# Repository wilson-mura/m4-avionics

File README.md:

# Martlet IV Avionics

This repository contains all the avionics for Martlet 4, including system 
design, documentation, schematics, PCBs, and firmware.

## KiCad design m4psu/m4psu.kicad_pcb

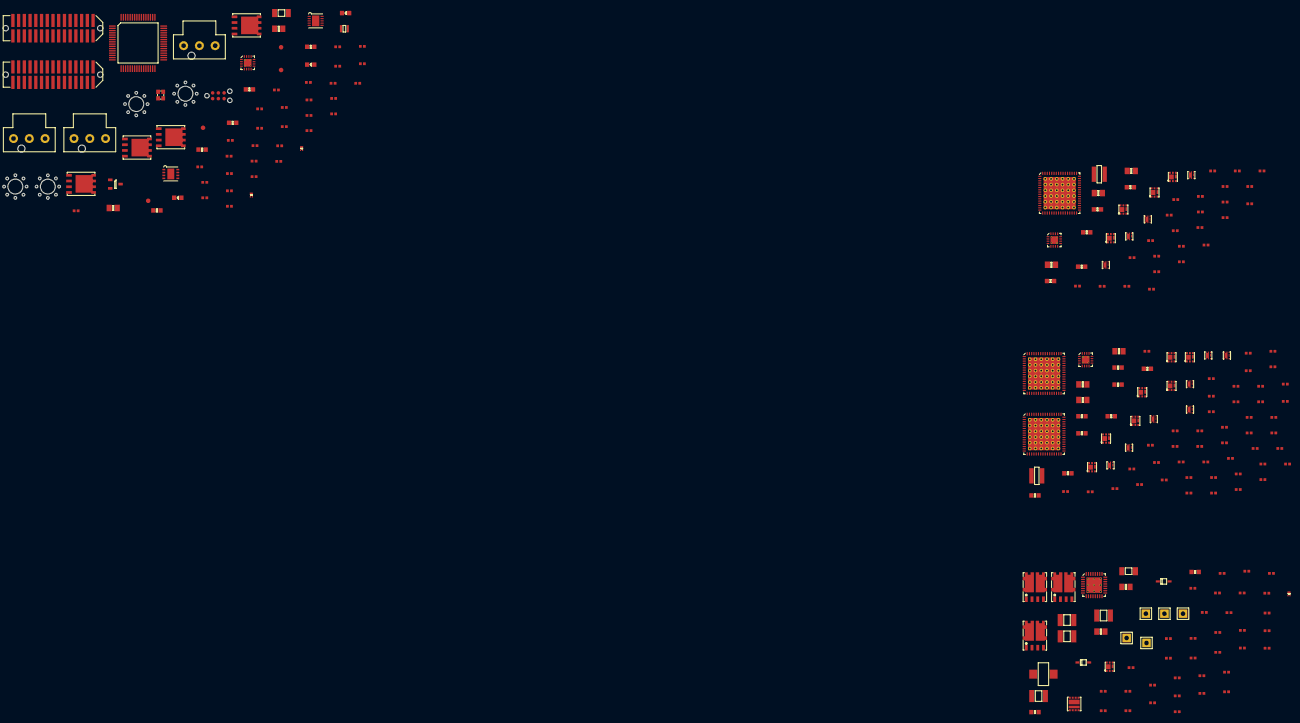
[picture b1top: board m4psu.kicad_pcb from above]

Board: 2 copper layers, 246 parts (0 on the bottom side), 161 nets, no tracks yet.

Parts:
C1, C2: 10p; 0402
C3, C5, C6, C8, C9, C10, C11, C22, C25, C29, C30, C32, C33, C34, C37, C42, C45, C46, C49, C50, C51, C52, C54, C55, C56, C57, C58: 100n; 0402
C4: 4µ7; 0402
C7, C43, C48: 1µ; 0402
C12, C13: 2µ2; 0402
C14, C17: 22µ; 0805
C15, C18, C19, C20, C23, C38: 100n; 0603
C16, C26, C39: 3n3; 0402
C21, C35: 10u; 0805
C24, C31, C36: 10n; 0402
C27, C28, C40, C41: 22u; 0805
C44, C64: 2µ2; 0805
C47: 1µ5; 0603
C53: 100p; 0402
C59, C60, C62, C63: 10µ; 1210
C61: 22p; 0402
D1: RED; 0603-LED
D2: YLW; 0603-LED
D3: GRN; 0603-LED
D4, D5: SCHOTTKY; SOD-323
IC1: MCP2562; DFN-8-EP-MICROCHIP
IC2: STM32F405RxTx; LQFP-64
IC3: TPS62152; QFN-16-EP-TI
IC4: LTC4151; DFN-10-EP-LT
IC5: TLV76012; SOT-23
IC6: TPS62132; QFN-16-EP-TI
IC7, IC8, IC10: LTC2975; QFN-64-EP-LTC-UP
IC9: TPS62133; QFN-16-EP-TI
IC11: BQ40Z60; QFN-32-EP-TI
J1: WEST TOP; TFML-115-02-L-D-LC
J2: EAST TOP; TFML-115-02-L-D-LC
J3: SUPPLY; ULTRA-FIT-01x03
J4: VALVES; ULTRA-FIT-01x03
J5: CHG; ULTRA-FIT-01x03
J6: BAT+; SIL-254P-01
J7: TAP3; SIL-254P-01
J8: TAP2; SIL-254P-01
J9: TAP1; SIL-254P-01
J10: BAT-; SIL-254P-01
L1: 3µ3; VLS201610HBX-1
L2, L3: 2u2; XFL4020
L4: 2µ2; SRP5030T
P1: SWD_TC; TC2030-NL
Q1, Q2, Q3, Q5: PFET; PowerPAK-SO-8
Q4, Q6, Q33: NFET; SOT-883-B
Q7, Q9, Q11, Q13, Q15, Q17, Q19, Q21, Q23, Q25, Q27: NFET; PowerPAK-SC-75-6L-Single
Q8, Q10, Q12, Q14, Q16, Q18, Q20, Q22, Q24, Q26, Q28: PFET; SON2x2
Q29, Q30, Q32: NFET2; PowerFLAT-5x6
Q31: SiZ340DT; PowerPair-3x3
Q34: NFET; SON2x2N
R1, R2: 100k; 0402
R3, R5, R6, R7: 100; 0402
R4, R8, R9: 4k7; 0402
R10, R98: 2m; 1206
R11, R15: 47k; 0402
R12, R16, R19, R20, R21, R22, R23, R25, R26, R31, R32, R33, R34, R35, R37, R38, R63, R64, R65, R66, R67, R69, R70: 10k; 0402
R13, R14, R17, R18, R27, R29, R39, R41, R43, R45, R47, R49, R51, R53, R55, R57, R59, R61, R71, R73, R75, R77, R79, R81, R83, R85: 33k; 0402
R24, R36, R68: 5k49; 0402
R28, R40, R44, R48, R52, R56, R60, R72, R76, R80, R84: 1M; 0402
R30, R42, R46, R50, R54, R58, R62, R74, R78, R82, R86, R99: 10m; 0603
R87, R88, R92, R93, R94, R95: 100R; 0402
R89, R100, R105: 10M; 0402
R90, R96, R104: 5K1; 0402
R91, R97: 10R; 0402
R101: 330K; 0402
R102: 56K2; 0402
R103: 10K; 0402
R106: 100K; 0402
R107: 2R; 0402
R108: 120; 0603
TP1, TP2, TP3, TP4: TESTPAD
X1, X2, X3, X4: HOLE; M3_MOUNT
Y1: 26M; XTAL-20x16

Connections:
3v3: C4.2, C5.2, C6.2, C7.2, C8.2, C9.2, C10.2, C11.2, C17.2, IC1.5, IC2.1, IC2.13, IC2.19, IC2.32, IC2.48, IC2.64, IC3.7, IC3.14, L1.2, P1.1, R1.2, R4.2, R8.2, R9.2
3v3_B: C22.2, C27.1, C28.1, C30.2, C34.2, IC6.14, IC7.9, IC7.10, IC7.11, IC7.12, IC7.55, IC7.56, IC8.9, IC8.10, IC8.11, IC8.12, IC8.35, IC8.55, IC8.56, IC10.10, IC10.11, IC10.12, L2.2, Q8.S, Q10.S, Q12.S, Q14.S, Q16.S, Q18.S, Q20.S, R19.1, R20.1, R21.1, R22.1, R23.1, R24.1, R25.1, R26.1, R27.1, R29.1, R31.1, R32.1, R33.1, R34.1, R35.1, R36.1, R37.1, R38.1, R39.1, R41.1, R43.1, R45.1, R47.1, R49.1, R51.1, R53.1, R55.1, R57.1, R59.1, R61.1, R63.1, R64.1, R65.1, R66.1, R67.1, R68.1, R69.1, R70.1
5v_B: C40.1, C41.1, IC9.14, IC10.9, IC10.55, IC10.56, L3.2, Q22.S, Q24.S, Q26.S, Q28.S, R71.1, R73.1, R75.1, R77.1, R79.1, R81.1, R83.1, R85.1
/3v3/ISNS0+: IC7.1, IC7.41, Q8.D, R30.2
/3v3/ISNS1+: IC7.43, IC7.63, Q10.D, R42.2
/3v3/ISNS2+: IC7.45, IC7.61, Q12.D, R46.2
/3v3/ISNS3+: IC7.47, IC7.49, Q14.D, R50.2
/3v3/ISNS4+: IC8.1, IC8.41, Q16.D, R54.2
/3v3/ISNS5+: IC8.43, IC8.63, Q18.D, R58.2
/3v3/ISNS6+: IC8.45, IC8.61, Q20.D, R62.2
/3v3/VEN_0: IC7.3, Q7.G, R27.2, R28.1
/3v3/VEN_1: IC7.4, Q9.G, R39.2, R40.1
/3v3/VEN_2: IC7.5, Q11.G, R43.2, R44.1
/3v3/VEN_3: IC7.6, Q13.G, R47.2, R48.1
/3v3/VEN_4: IC8.3, Q15.G, R51.2, R52.1
/3v3/VEN_5: IC8.4, Q17.G, R55.2, R56.1
/3v3/VEN_6: IC8.5, Q19.G, R59.2, R60.1
/3v3_AUX1: IC8.44, J1.15, R58.1
/3v3_AUX2: IC8.46, J1.17, R62.1
/3v3_DL: IC7.44, J1.7, R42.1
/3v3_FC: IC7.46, J1.9, R46.1
/3v3_PYRO: IC8.42, J1.13, R54.1
/3v3_RADIO: IC7.48, J1.11, R50.1
/3v3_TOP: IC7.42, J1.5, R30.1
/5v/ISNS7+: IC10.1, IC10.41, Q22.D, R74.2
/5v/ISNS8+: IC10.43, IC10.63, Q24.D, R78.2
/5v/ISNS9+: IC10.45, IC10.61, Q26.D, R82.2
/5v/ISNS10+: IC10.47, IC10.49, Q28.D, R86.2
/5v/VEN_7: IC10.3, Q21.G, R71.2, R72.1
/5v/VEN_8: IC10.4, Q23.G, R75.2, R76.1
/5v/VEN_9: IC10.5, Q25.G, R79.2, R80.1
/5v/VEN_10: IC10.6, Q27.G, R83.2, R84.1
/5v_AUX1: IC10.44, J2.17, R78.1
/5v_AUX2: IC10.46, J2.19, R82.1
/5v_CAM1: IC10.48, J2.21, J2.23, R86.1
/5v_CAN: C3.1, IC1.3, J1.22
/5v_RADIO: IC10.42, J2.15, R74.1
/12v_DIV: IC2.21, R11.2, R12.1
/12v_DL: C20.2, IC5.1, J2.13, R11.1
/CAN+: IC1.7, J1.26, R108.2
/CAN-: IC1.6, J1.24, R108.1
/CAN_RXD: IC1.4, IC2.61
/CAN_TXD: IC1.1, IC2.62
/EN_POWER: IC2.43, Q6.G, R18.1
/EN_PYRO: IC2.16, Q4.G, R14.2
/JTCK: IC2.49, J1.8, P1.4
/JTDI: IC2.50, J1.10
/JTDR: IC2.55, J1.12
/JTMS: IC2.46, J1.6, P1.2
/LED_GRN: IC2.11, R7.1
/LED_RED: IC2.9, R5.1
/LED_YLW: IC2.10, R6.1
/PWR: J2.25, R1.1, R2.1
/PYRO_SO: J3.1, J3.2, J3.3, Q1.D, Q2.D, Q3.D, R15.1
/SCL: IC2.41, IC4.6, IC7.30, IC8.30, IC10.30, R8.1, R88.1, TP2.1
/SDA: IC2.40, IC4.7, IC7.29, IC8.29, IC10.29, R4.1, R87.1, TP1.1
/SO_DIV: IC2.22, R15.2, R16.1
/V_SHORE: J5.1, J5.2, Q33.S, Q34.S, R103.2, R105.1, R106.1, R107.1
/charger/ACFET: IC11.29, R104.2
/charger/ACP: IC11.31, R103.1
/charger/BATT1: J9.1, R95.2
/charger/BATT2: J8.1, R94.2
/charger/BATT3: J7.1, R93.2
/charger/BATT4: C45.1, J6.1, Q29.S1, Q29.S2, Q30.S1, R89.1, R92.2, R97.2
/charger/CHG: IC11.32, R90.2
/charger/DSG: IC11.30, R96.2
/charger/VCHARGE: C62.2, C63.2, Q31.D1, Q34.D, R91.2
/~ALERT: IC2.42, IC7.31, IC8.31, IC10.31, IC11.14, R9.1, TP3.1
/~RST: IC2.7, P1.3
/~WAKE: IC2.14, R2.2
GND: C1.1, C2.1, C3.2, C4.1, C5.1, C6.1, C7.1, C8.1, C9.1, C10.1, C11.1, C12.2, C13.2, C14.1, C15.1, C16.1, C17.1, C18.1, C19.1, C20.1, C21.2, C22.1, C23.2, C24.1, C25.1, C26.2, C27.2, C28.2, C30.1, C31.1, C32.1, C34.1, C35.2, C36.1, C37.1, C38.2, C39.2, C40.2, C41.2, C53.2, C54.2, C59.2, C60.2, C62.1, C63.1, C64.2, D1.1, D2.1, D3.1, IC1.2, IC1.8, IC1.EP, IC2.12, IC2.18, IC2.60, IC2.63, IC3.5, IC3.6, IC3.8, IC3.15, IC3.16, IC3.EP, IC4.3, IC4.4, IC4.5, IC4.9, IC4.EP, IC5.3, IC6.5, IC6.6, IC6.7, IC6.8, IC6.15, IC6.16, IC6.EP, IC7.2, IC7.15, IC7.16, IC7.19, IC7.20, IC7.21, IC7.27, IC7.28, IC7.34, IC7.36, IC7.37, IC7.39, IC7.50, IC7.52, IC7.59, IC7.60, IC7.62, IC7.64, IC7.EP, IC8.2, IC8.15, IC8.16, IC8.19, IC8.20, IC8.21, IC8.27, IC8.28, IC8.34, IC8.36, IC8.37, IC8.39, IC8.47, IC8.48, IC8.49, IC8.50, IC8.52, IC8.59, IC8.60, IC8.62, IC8.64, IC8.EP, IC9.5, IC9.6, IC9.7, IC9.8, IC9.15, IC9.16, IC9.EP, IC10.2, IC10.15, IC10.16, IC10.19, IC10.20, IC10.21, IC10.27, IC10.28, IC10.34, IC10.35, IC10.36, IC10.37, IC10.39, IC10.50, IC10.52, IC10.59, IC10.60, IC10.62, IC10.64, IC10.EP, IC11.7, IC11.24, J1.1, J1.2, J1.3, J1.4, J1.27, J1.28, J1.29, J1.30, J2.1, J2.2, J2.3, J2.4, J2.27, J2.28, J2.29, J2.30, J4.1, J4.2, J4.3, J5.3, P1.5, Q4.S, Q6.S, Q7.S, Q9.S, Q11.S, Q13.S, Q15.S, Q17.S, Q19.S, Q21.S, Q23.S, Q25.S, Q27.S, Q31.S2, Q33.G, R12.2, R14.1, R16.2, R18.2, R28.2, R40.2, R44.2, R48.2, R52.2, R56.2, R60.2, R72.2, R76.2, R80.2, R84.2, R98.1, R106.2, TP4.1, Y1.2, Y1.4
unnamed: C1.2, IC2.5, Y1.1
unnamed: C2.2, R3.1, Y1.3
unnamed: C12.1, IC2.47
unnamed: C13.1, IC2.31
unnamed: C16.2, IC3.9
unnamed: C24.2, IC7.51
unnamed: C25.2, IC7.13, IC7.14
unnamed: C26.1, IC6.9
unnamed: C29.1, IC7.38
unnamed: C29.2, IC7.40
unnamed: C31.2, IC8.51
unnamed: C32.2, IC8.13, IC8.14
unnamed: C33.1, IC8.38
unnamed: C33.2, IC8.40
unnamed: C36.2, IC10.51
unnamed: C37.2, IC10.13, IC10.14
unnamed: C39.1, IC9.9
unnamed: C42.1, IC10.38
unnamed: C42.2, IC10.40
unnamed: C43.2, IC11.22, R91.1
unnamed: C44.2, IC11.2
unnamed: C45.2, C55.2
unnamed: C46.1, D4.1, IC11.28
unnamed: C46.2, IC11.26, L4.2, Q31.S1D2
unnamed: C47.1, D4.2, IC11.23
unnamed: C48.1, D5.1, IC11.1
unnamed: C49.1, IC11.3, R92.1
unnamed: C49.2, C50.1, IC11.4, R93.1
unnamed: C50.2, C51.1, IC11.5, R94.1
unnamed: C51.2, C52.1, IC11.6, R95.1
unnamed: C56.2, C57.1, IC11.20, L4.1, R99.1
unnamed: C61.2, IC11.18, R101.2, R102.1
unnamed: C64.1, R107.2
unnamed: D1.2, R5.2
unnamed: D2.2, R6.2
unnamed: D3.2, R7.2
unnamed: D5.2, R97.1
unnamed: IC2.6, R3.2
unnamed: IC3.1, IC3.2, IC3.3, L1.1
unnamed: IC4.10, Q1.S, Q2.S, Q3.S, R10.1, R13.2
unnamed: IC6.1, IC6.2, IC6.3, L2.1
unnamed: IC7.18, R24.2
unnamed: IC7.22, R23.2
unnamed: IC7.23, R21.2
unnamed: IC7.24, R25.2
unnamed: IC7.25, R19.2
unnamed: IC7.26, R26.2
unnamed: IC7.32, R22.2
unnamed: IC7.33, R20.2
unnamed: IC8.18, R36.2
unnamed: IC8.22, R35.2
unnamed: IC8.23, R33.2
unnamed: IC8.24, R37.2
unnamed: IC8.25, R31.2
unnamed: IC8.26, R38.2
unnamed: IC8.32, R34.2
unnamed: IC8.33, R32.2
unnamed: IC9.1, IC9.2, IC9.3, L3.1
unnamed: IC10.18, R68.2
unnamed: IC10.22, R67.2
unnamed: IC10.23, R65.2
unnamed: IC10.24, R69.2
unnamed: IC10.25, R63.2
unnamed: IC10.26, R70.2
unnamed: IC10.32, R66.2
unnamed: IC10.33, R64.2
unnamed: IC11.16, R87.2
unnamed: IC11.17, R88.2
unnamed: IC11.25, Q31.G2
unnamed: IC11.27, Q31.G1
unnamed: Q1.G, Q2.G, Q3.G, Q4.D, R13.1
unnamed: Q5.G, Q6.D, R17.1
unnamed: Q7.D, Q8.G, R29.2
unnamed: Q9.D, Q10.G, R41.2
unnamed: Q11.D, Q12.G, R45.2
unnamed: Q13.D, Q14.G, R49.2
unnamed: Q15.D, Q16.G, R53.2
unnamed: Q17.D, Q18.G, R57.2
unnamed: Q19.D, Q20.G, R61.2
unnamed: Q21.D, Q22.G, R73.2
unnamed: Q23.D, Q24.G, R77.2
unnamed: Q25.D, Q26.G, R81.2
unnamed: Q27.D, Q28.G, R85.2
unnamed: Q29.D1, Q29.D2, Q30.D1, Q30.D2, Q32.D1, Q32.D2
unnamed: Q29.G1, Q29.G2, Q30.G1, R89.2, R90.1
unnamed: Q30.G2, Q32.G1, Q32.G2, R96.1, R100.2
unnamed: Q33.D, Q34.G, R104.1, R105.2
PGND: C43.1, C44.1, C47.2, C48.2, C52.2, C53.1, C54.1, C56.1, C58.1, IC11.8, IC11.9, IC11.21, IC11.EP, J10.1, R98.2, R102.2
VBATT: C14.2, C15.2, C18.2, C55.1, C57.2, C58.2, C59.1, C60.1, C61.1, IC3.10, IC3.11, IC3.12, IC3.13, IC4.1, IC4.2, IC11.19, Q5.S, Q30.S2, Q32.S1, Q32.S2, R10.2, R17.2, R99.2, R100.1, R101.1
VCC: C19.2, C21.1, C23.1, C35.1, C38.1, IC5.2, IC6.10, IC6.11, IC6.12, IC6.13, IC9.10, IC9.11, IC9.12, IC9.13, Q5.D

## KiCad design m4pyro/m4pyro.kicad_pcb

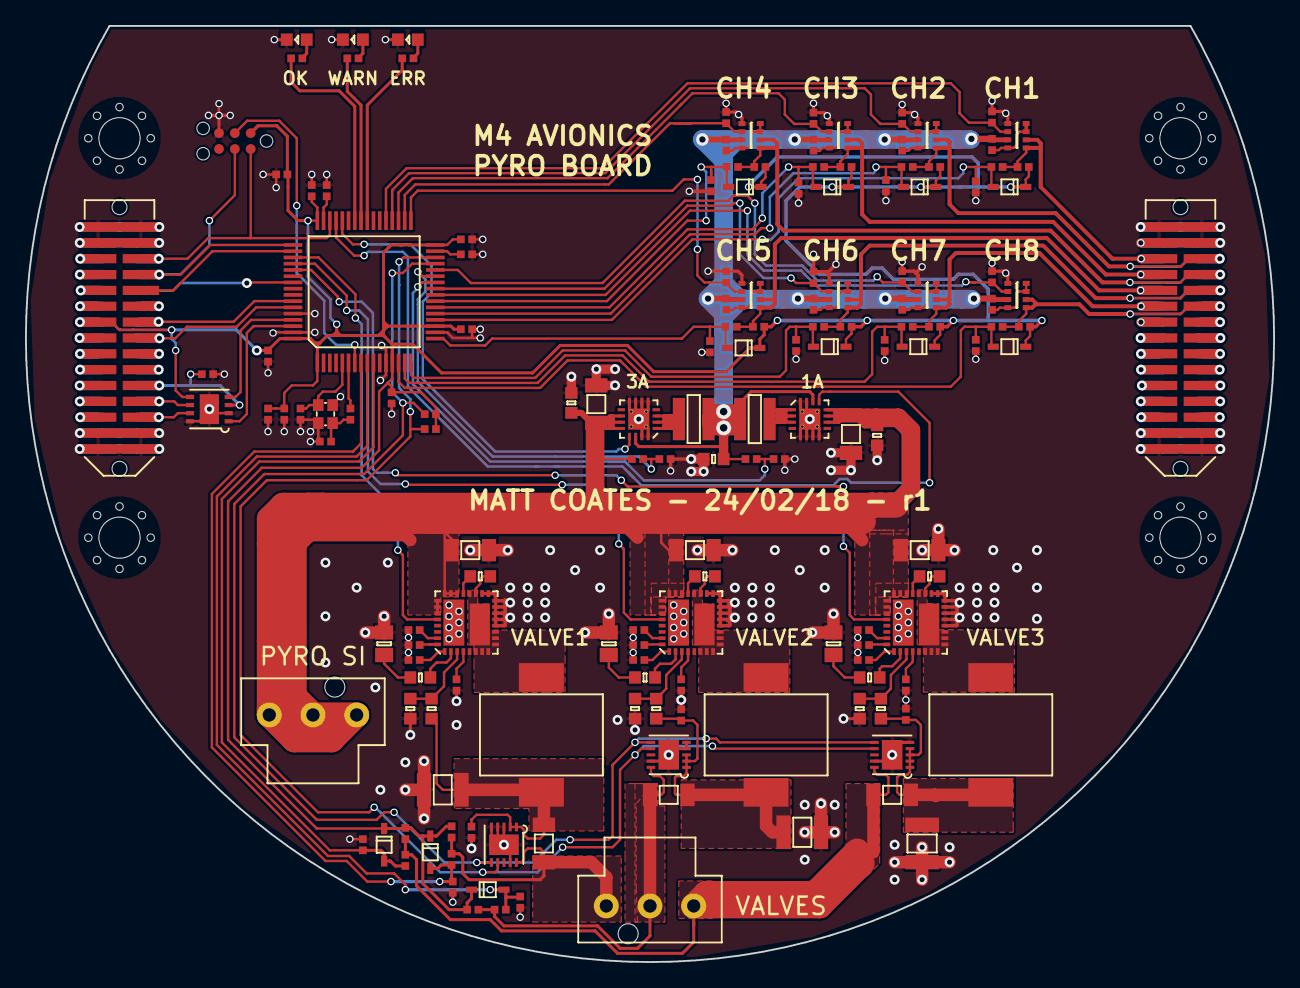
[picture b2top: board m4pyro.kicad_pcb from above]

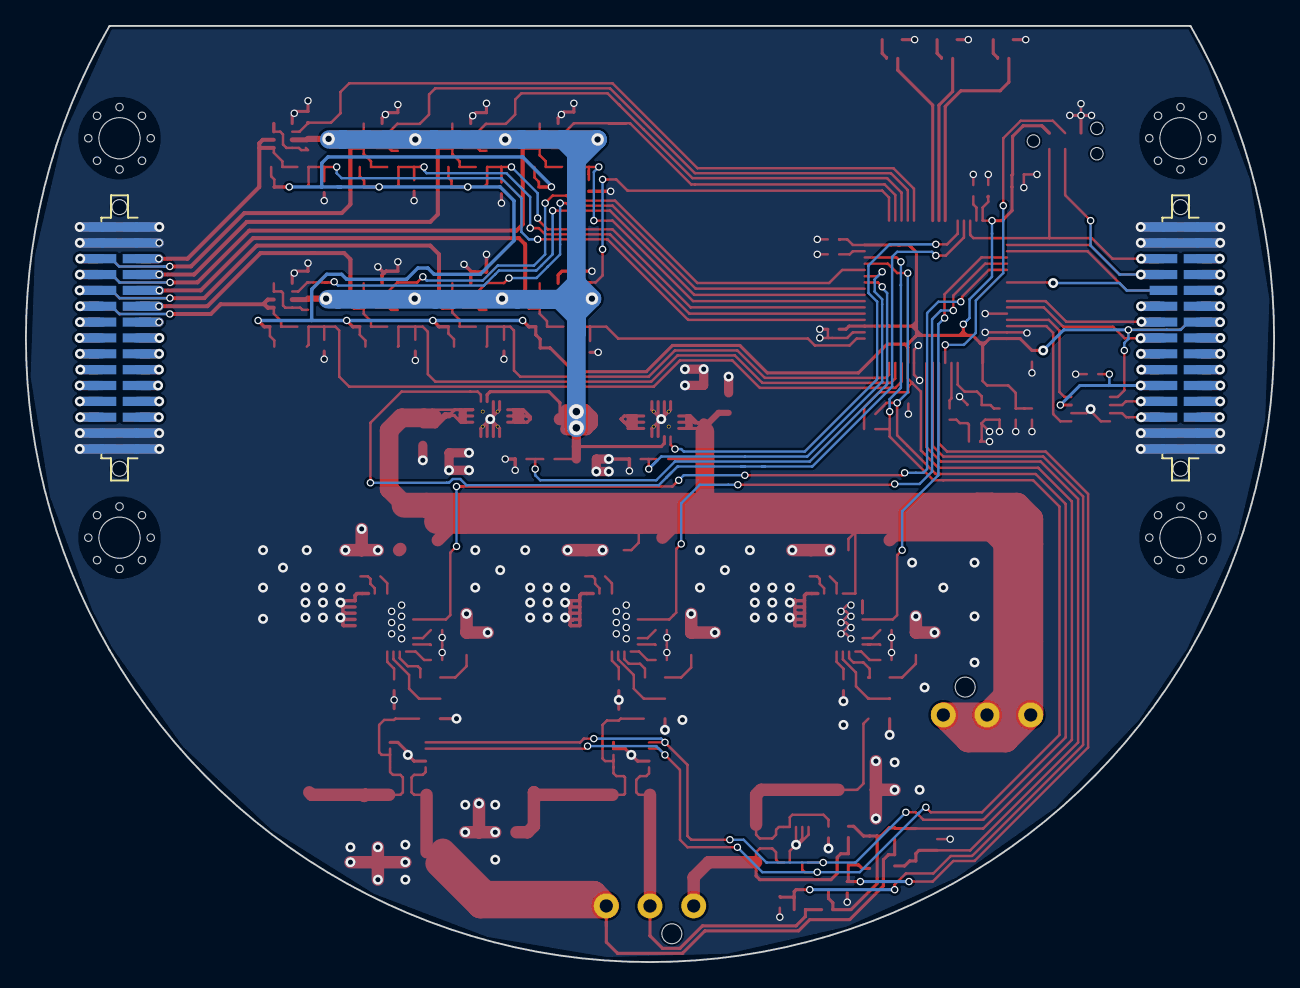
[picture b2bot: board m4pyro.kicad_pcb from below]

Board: 2 copper layers, 100.0 x 75.0 mm, 165 parts (2 on the bottom side), 133 nets.

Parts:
C1, C2: 10p; 0402
C3: 4µ7; 0402
C4, C5, C7, C8, C9, C10, C15, C19, C20, C21, C22, C23, C24, C25, C26, C29, C36, C43, C48, C49, C50: 100n; 0402
C6, C28, C35, C42: 1µ; 0402
C11, C18: 2µ2; 0402
C12, C14, C27, C34, C41: 10µ; 1206
C13, C17, C30, C37, C44: 100n; 0603
C16: 22µ; 0603
C31, C38, C45: 22n; 0402
C32, C39, C46: 1.2u; 0805
C33, C40, C47: 100µ; 1210
D1: RED; 0603-LED
D2: YLW; 0603-LED
D3: GRN; 0603-LED
D4, D5, D6, D7, D8, D9, D10, D11, D12, D13, D14: PMEG3005AEA; SOD-323
IC1: STM32F405RxTx; LQFP-64
IC2: TPS62133; QFN-16-EP-TI
IC3: MCP2562; DFN-8-EP-MICROCHIP
IC4: TPS62153; QFN-16-EP-TI
IC5, IC7, IC9: ADP2389; ADP2389ACPZ-R7
IC6, IC8, IC10: LTC4151; DFN-10-EP-LT
J1: WEST TOP; TFML-115-02-L-D-LC
J2: WEST BOT; SFML-115-02-L-D
J3: EAST TOP; TFML-115-02-L-D-LC
J4: EAST BOT; SFML-115-02-L-D
J5: SUPPLY; ultra-fit-01x03
J6: VALVES; ultra-fit-01x03
L1, L2: 2µ2; XFL4020
L3, L4, L5: 2µ2; WE-HCC-1090
P1: SWD_TC; TC2030-NL
Q1, Q2, Q3, Q4, Q5, Q6, Q7, Q8: Si5515CDC; ChipFET-1206-8
R1, R2, R3, R4: 100; 0402
R5, R9, R11, R12, R13, R14, R15, R16, R17, R18, R19, R20, R21, R22, R23, R24, R25, R26, R27, R28, R31, R32, R35, R36, R39, R40, R61, R62, R63: 10k; 0402
R6, R8, R29, R30, R33, R34, R37, R38, R58, R59, R60: 1k; 0402
R7: 47k; 0402
R10: 3k3; 0402
R41, R42: 4k7; 0402
R43, R48, R53: 100k; 0402
R44, R49, R54: 68k; 0603
R45, R50, R55: 47.5k; 0603
R46, R51, R56: 2.5k; 0603
R47, R52, R57: 5m; 1206
R64, R65, R66: 82.5k; 0402
X2, X3, X4, X5: HOLE; M3_MOUNT
Y1: 26M; XTAL-20x16

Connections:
3v3: C3.2, C4.2, C5.2, C6.2, C7.2, C8.2, C9.2, C10.2, D4.1, D5.1, D6.1, D7.1, D8.1, D9.1, D10.1, D11.1, D12.1, D13.1, D14.1, IC1.1, IC1.13, IC1.19, IC1.32, IC1.48, IC1.64, IC3.5, J1.13, J2.13, P1.1, R6.2, R8.2, R29.2, R30.2, R33.2, R34.2, R37.2, R38.2, R41.2, R42.2, R58.2, R59.2, R60.2
/1A_EN: IC1.45, IC4.13
/3A_EN: IC1.44, IC2.13
/3v3_AUX1: J1.15, J2.15
/3v3_AUX2: J1.17, J2.17
/3v3_DL: J1.7, J2.7
/3v3_FC: J1.9, J2.9
/3v3_RADIO: J1.11, J2.11
/3v3_TOP: J1.5, J2.5
/5v_AUX1: J3.17, J4.17
/5v_AUX2: J3.19, J4.19
/5v_CAM1: J3.21, J4.21
/5v_CAM2: J3.23, J4.23
/5v_CAN: C15.1, IC3.3, J1.22, J2.22
/5v_RADIO: J3.15, J4.15
/12v_DL: J3.13, J4.13
/BUS: C16.1, IC2.14, IC4.14, L1.2, L2.2, Q1.3, Q2.3, Q3.3, Q4.3, Q5.3, Q6.3, Q7.3, Q8.3, R9.1, R15.1, R16.1, R17.1, R18.1, R25.1, R26.1, R27.1, R28.1
/BUS_DIV: IC1.26, R9.2, R10.1
/CAN+: IC3.7, J1.26, J2.26
/CAN-: IC3.6, J1.24, J2.24
/CAN_RXD: IC1.61, IC3.4
/CAN_TXD: IC1.62, IC3.1
/CH1: IC1.37, Q7.2, R14.1
/CH1_CONT: C19.2, D4.2, IC1.20, R19.2
/CH2: IC1.36, Q6.2, R23.1
/CH2_CONT: C21.2, D6.2, IC1.21, R31.2
/CH3: IC1.35, Q5.2, R13.1
/CH3_CONT: C23.2, D8.2, IC1.22, R35.2
/CH4: IC1.34, Q8.2, R24.1
/CH4_CONT: C25.2, D10.2, IC1.23, R39.2
/CH5: IC1.33, Q3.2, R12.1
/CH5_CONT: C20.2, D5.2, IC1.17, R20.2
/CH6: IC1.25, Q2.2, R21.1
/CH6_CONT: C22.2, D7.2, IC1.16, R32.2
/CH7: IC1.28, Q1.2, R11.1
/CH7_CONT: C24.2, D9.2, IC1.15, R36.2
/CH8: IC1.24, Q4.2, R22.1
/CH8_CONT: C26.2, D11.2, IC1.14, R40.2
/JTCK: IC1.49, J1.8, J2.8, P1.4
/JTDI: IC1.50, J1.10
/JTDO: IC1.55, J2.10
/JTDR: J1.12, J2.12
/JTMS: IC1.46, J1.6, J2.6, P1.2
/LED_GRN: IC1.42, R4.1
/LED_RED: IC1.40, R2.1
/LED_YLW: IC1.41, R3.1
/PWR: J3.25, J4.25
/PYRO1: J3.5, J4.5, Q7.5, Q7.6, R6.1, R19.1
/PYRO2: J3.6, J4.6, Q6.5, Q6.6, R29.1, R31.1
/PYRO3: J3.7, J4.7, Q5.5, Q5.6, R33.1, R35.1
/PYRO4: J3.8, J4.8, Q8.5, Q8.6, R37.1, R39.1
/PYRO5: J3.9, J4.9, Q3.5, Q3.6, R8.1, R20.1
/PYRO6: J3.10, J4.10, Q2.5, Q2.6, R30.1, R32.1
/PYRO7: J3.11, J4.11, Q1.5, Q1.6, R34.1, R36.1
/PYRO8: J3.12, J4.12, Q4.5, Q4.6, R38.1, R40.1
/PYRO_SI: C12.2, C13.2, C14.2, C17.2, C27.2, C34.2, C41.2, IC2.10, IC2.11, IC2.12, IC4.10, IC4.11, IC4.12, IC5.22, IC5.23, IC5.24, IC5.25, IC5.26, IC5.27, IC7.22, IC7.23, IC7.24, IC7.25, IC7.26, IC7.27, IC9.22, IC9.23, IC9.24, IC9.25, IC9.26, IC9.27, J5.1, J5.2, J5.3, R7.1
/RSVD1: J1.18, J2.18
/RSVD2: J1.19, J2.19
/RSVD3: J1.20, J2.20
/RSVD4: J1.21, J2.21
/RSVD5: J1.23, J2.23
/RSVD6: J1.25, J2.25
/RSVD7: J3.14, J4.14
/RSVD8: J3.16, J4.16
/RSVD9: J3.18, J4.18
/RSVD10: J3.20, J4.20
/RSVD11: J3.22, J4.22
/RSVD12: J3.24, J4.24
/RSVD13: J3.26, J4.26
/SCL: IC1.29, IC6.6, IC8.6, IC10.6, R42.1
/SDA: IC1.30, IC6.7, IC8.7, IC10.7, R41.1
/SI_DIV: IC1.27, R5.1, R7.2
/UART_RX: IC1.59, J1.16, J2.16
/UART_TX: IC1.58, J1.14, J2.14
/V1_CONT: C48.2, D12.2, IC1.8, R61.2
/V1_FIRE: IC1.51, IC5.28
/V2_CONT: C49.2, D13.2, IC1.9, R62.2
/V2_FIRE: IC1.52, IC7.28
/V3_CONT: C50.2, D14.2, IC1.10, R63.2
/V3_FIRE: IC1.53, IC9.28
/VALVE_1: IC6.10, J6.1, R47.1, R58.1, R61.1
/VALVE_2: IC8.10, J6.2, R52.1, R59.1, R62.1
/VALVE_3: IC10.10, J6.3, R57.1, R60.1, R63.1
/V_1_SUPPLY: C29.2, C33.2, IC6.1, IC6.2, L3.2, R45.2, R47.2
/V_2_SUPPLY: C36.2, C40.2, IC8.1, IC8.2, IC8.3, L4.2, R50.2, R52.2
/V_3_SUPPLY: C43.2, C47.2, IC10.1, IC10.2, IC10.3, IC10.4, L5.2, R55.2, R57.2
/~RST: IC1.7, P1.3
GND: C1.1, C2.1, C3.1, C4.1, C5.1, C6.1, C7.1, C8.1, C9.1, C10.1, C11.2, C12.1, C13.1, C14.1, C15.2, C16.2, C17.1, C18.2, C19.1, C20.1, C21.1, C22.1, C23.1, C24.1, C25.1, C26.1, C27.1, C28.1, C29.1, C31.1, C32.1, C33.1, C34.1, C35.1, C36.1, C38.1, C39.1, C40.1, C41.1, C42.1, C43.1, C45.1, C46.1, C47.1, C48.1, C49.1, C50.1, D1.1, D2.1, D3.1, IC1.12, IC1.18, IC1.60, IC1.63, IC2.5, IC2.6, IC2.7, IC2.8, IC2.15, IC2.16, IC2.EP, IC3.2, IC3.8, IC3.EP, IC4.5, IC4.6, IC4.7, IC4.8, IC4.15, IC4.16, IC4.EP, IC5.5, IC5.12, IC5.13, IC5.14, IC5.15, IC5.16, IC5.17, IC5.18, IC5.33, IC6.3, IC6.4, IC6.5, IC6.9, IC6.EP, IC7.5, IC7.12, IC7.13, IC7.14, IC7.15, IC7.16, IC7.17, IC7.18, IC7.33, IC8.4, IC8.5, IC8.9, IC8.EP, IC9.5, IC9.12, IC9.13, IC9.14, IC9.15, IC9.16, IC9.17, IC9.18, IC9.33, IC10.5, IC10.9, IC10.EP, J1.1, J1.2, J1.3, J1.4, J1.27, J1.28, J1.29, J1.30, J2.1, J2.2, J2.3, J2.4, J2.27, J2.28, J2.29, J2.30, J3.1, J3.2, J3.3, J3.4, J3.27, J3.28, J3.29, J3.30, J4.1, J4.2, J4.3, J4.4, J4.27, J4.28, J4.29, J4.30, P1.5, Q1.1, Q2.1, Q3.1, Q4.1, Q5.1, Q6.1, Q7.1, Q8.1, R5.2, R10.2, R11.2, R12.2, R13.2, R14.2, R21.2, R22.2, R23.2, R24.2, R43.1, R46.2, R48.1, R51.2, R53.1, R56.2, R64.1, R65.1, R66.1, Y1.2, Y1.4
unnamed: C1.2, IC1.5, Y1.1
unnamed: C2.2, R1.1, Y1.3
unnamed: C11.1, IC1.47
unnamed: C18.1, IC1.31
unnamed: C28.2, IC5.4
unnamed: C30.1, IC5.21
unnamed: C30.2, IC5.6, IC5.7, IC5.8, IC5.9, IC5.10, IC5.11, IC5.19, IC5.20, IC5.34, L3.1
unnamed: C31.2, IC5.1
unnamed: C32.2, R44.2
unnamed: C35.2, IC7.4
unnamed: C37.1, IC7.21
unnamed: C37.2, IC7.6, IC7.7, IC7.8, IC7.9, IC7.10, IC7.11, IC7.19, IC7.20, IC7.34, L4.1
unnamed: C38.2, IC7.1
unnamed: C39.2, R49.2
unnamed: C42.2, IC9.4
unnamed: C44.1, IC9.21
unnamed: C44.2, IC9.6, IC9.7, IC9.8, IC9.9, IC9.10, IC9.11, IC9.19, IC9.20, IC9.34, L5.1
unnamed: C45.2, IC9.1
unnamed: C46.2, R54.2
unnamed: D1.2, R2.2
unnamed: D2.2, R3.2
unnamed: D3.2, R4.2
unnamed: IC1.6, R1.2
unnamed: IC2.1, IC2.2, IC2.3, L1.1
unnamed: IC4.1, IC4.2, IC4.3, L2.1
unnamed: IC5.2, R44.1
unnamed: IC5.3, R45.1, R46.1
unnamed: IC5.31, R64.2
unnamed: IC5.32, R43.2
unnamed: IC7.2, R49.1
unnamed: IC7.3, R50.1, R51.1
unnamed: IC7.31, R65.2
unnamed: IC7.32, R48.2
unnamed: IC9.2, R54.1
unnamed: IC9.3, R55.1, R56.1
unnamed: IC9.31, R66.2
unnamed: IC9.32, R53.2
unnamed: Q1.4, Q1.7, Q1.8, R15.2
unnamed: Q2.4, Q2.7, Q2.8, R25.2
unnamed: Q3.4, Q3.7, Q3.8, R16.2
unnamed: Q4.4, Q4.7, Q4.8, R26.2
unnamed: Q5.4, Q5.7, Q5.8, R17.2
unnamed: Q6.4, Q6.7, Q6.8, R27.2
unnamed: Q7.4, Q7.7, Q7.8, R18.2
unnamed: Q8.4, Q8.7, Q8.8, R28.2

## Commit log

2018-01-24 Initial commit of gcs
2018-01-24 Add local copies of fontawesome and update gitignores
2018-01-24 Fix typo in font-awesome css filename
2018-01-24 Final commit before switching over to react
2018-01-24 Switch from w3 to bootstrap
2018-01-24 Tidy up html example page, add node_modules
2018-01-24 Remove unnecessary files, add favicon and rename html file as index
2018-01-25 Restructure webapp files by using create-react-app
2018-01-25 Add favicon
2018-01-25 Removing node modules from git history
2018-01-25 Update readme with npm install instruction, remove old css
2018-01-25 Tidy python files in preparation for meeting, update manifest.json
2018-01-27 Begin structuring python code based on TOAD gcs
2018-01-28 First draft of usb packets
2018-02-02 changed the structure of the web app separating the client from the server
2018-02-02 trying to create a skeleton
2018-02-02 Ready to start writing some nice layout
2018-02-02 Add pipes and packets
2018-02-03 added add-kicad
2018-02-03 started datalogger and finalised interconnect layout
2018-02-04 Added a graph widges after trying several different libraries
2018-02-04 Testing some new components
2018-02-04 Begin m4fc
2018-02-04 moved pwr switch and removed chg from golbal interconnect
2018-02-04 Tidy m3fc schematic
2018-02-05 Add FC components to schematic
2018-02-05 Move rf amplifier to separate board
2018-02-05 Reorder app.route method
2018-02-05 Minor fixes
2018-02-07 Add print_json method and minor fixes
2018-02-07 Add pipe lists, create serial test
2018-02-07 ready socketio
2018-02-07 Forgot a line
2018-02-08 started pyro board
2018-02-09 added valve fire and monitor stuff, need to think about continuity
2018-02-10 pyro schematic almost done
2018-02-11 started pyro pcb
2018-02-15 strain gauge circuit added to data logger
2018-02-15 laying out pyro valve components
2018-02-16 added pcb template
2018-02-16 put down high current tracks
2018-02-16 added gnd vias and continuity circuits
2018-02-17 started mcu layout
2018-02-18 pcb progress
2018-02-21 continued pyro board layout
2018-02-23 made good progress on pyro routing
2018-02-24 routed pyro board
2018-02-24 added bom
2018-02-24 started PSU
2018-02-24 added ilim resistor to pyro board
2018-02-25 strain gauge filter circuit added
2018-02-25 updated pressure label, groundss
2018-02-25 Thermo circuitry added
2018-02-25 added annotations to test pads
2018-02-25 fixed second op amp
2018-02-25 Add ltspice simulation of ideal diode
2018-02-25 Update clock circuitry and separate 3v3 nets for radio and fc
2018-02-28 did dcdc converters
2018-03-01 finished psu schematic - needs review/checking
